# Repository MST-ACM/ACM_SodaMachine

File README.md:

# ACM Soda Machine Documentation
This documentation details all of information necessary to start, develop, maintain, and update the Soda Machine in CS 213.

## Dependencies
1. [Pyserial](https://github.com/pyserial/pyserial)
  + ```Pyserial``` handles the serial communication of authorization and logging characters between the Raspberry Pi and Arduino platforms in the soda machine.
2. [Pymysql](https://github.com/PyMySQL/PyMySQL)
  + ```Pymsql``` handles the connection to the SQL-lite database stored locally on the Raspberry Pi machine which stores the currency (i.e. how much money each user has).
3. [Libusb1](https://github.com/vpelletier/python-libusb1)
  + ```Libusb1``` handles the interfacing between the LCD screen and the Raspberry Pi so that the Raspberry Pi can write messages to the LCD.
4. [Evdev](https://python-evdev.readthedocs.io/en/latest/)
  + ```Evdev``` handles Kernel input interfacing for the magnetic strip reader when a user swipes their card.
5. [Nanpy](https://github.com/nanpy/nanpy)
  + ```Nanpy``` handles the direct throughput and communication to the arduino board through python.

## Installation
When migrating or reinstalling the system, please follow the following commands on the Raspberry Pi shell to install the main soda machine files ```NOT DEPENDENCIES```:
```
mkdir ~/pi/Soda-Machine/
cd ~/pi/Soda-Machine/
git init
git clone https://github.com/MST-ACM/ACM_SodaMachine_2.0.git
chmod +x main.py bin/smadmin bin/smdaemon
mv Documentation/sodamachine.init /etc/init.d/sodamachine
sudo update-rc.d sodamachine defaults
sudo service sodamachine restart
```
## Pseudocode Overview
1. The user swipes their Student ID into the magnetic strip reader which the magnetic strip reader translates to a ```Student ID```
2. ```Main.py``` performs a database lookup on the Student ID to determine if the user has the required funds.
3. If the database lookup is successful, the Raspberry Pi sends an authorization character to the Arduino using the serial connection.
  - If the database lookup is not successful the transaction fails and the Raspberry Pi resets it transaction state.
4. After the Arduino receives the authorization character, it waits for the user to press a button on the soda machine
  - If the user does not press a button after a certain amount of seconds, the transaction fails and the Raspberry Pi and Arduino reset their states.
5. After the user presses a button, the Arduino turns on the motor associated with the button until the soda is dispensed.
6. After the soda is dispensed, the Arduino sends a success character back to the Raspberry Pi so that the Raspberry Pi charges the user for the soda
  - The user is charged here instead of step 4 to prevent any errors with a soda failing to be dispensed.
7. Then, the Arduino and Raspberry Pi reset their states for the next transaction.

## Contribute
Please contact [acm@mst.edu](acm@mst.edu) if you would like to contribute to this project.

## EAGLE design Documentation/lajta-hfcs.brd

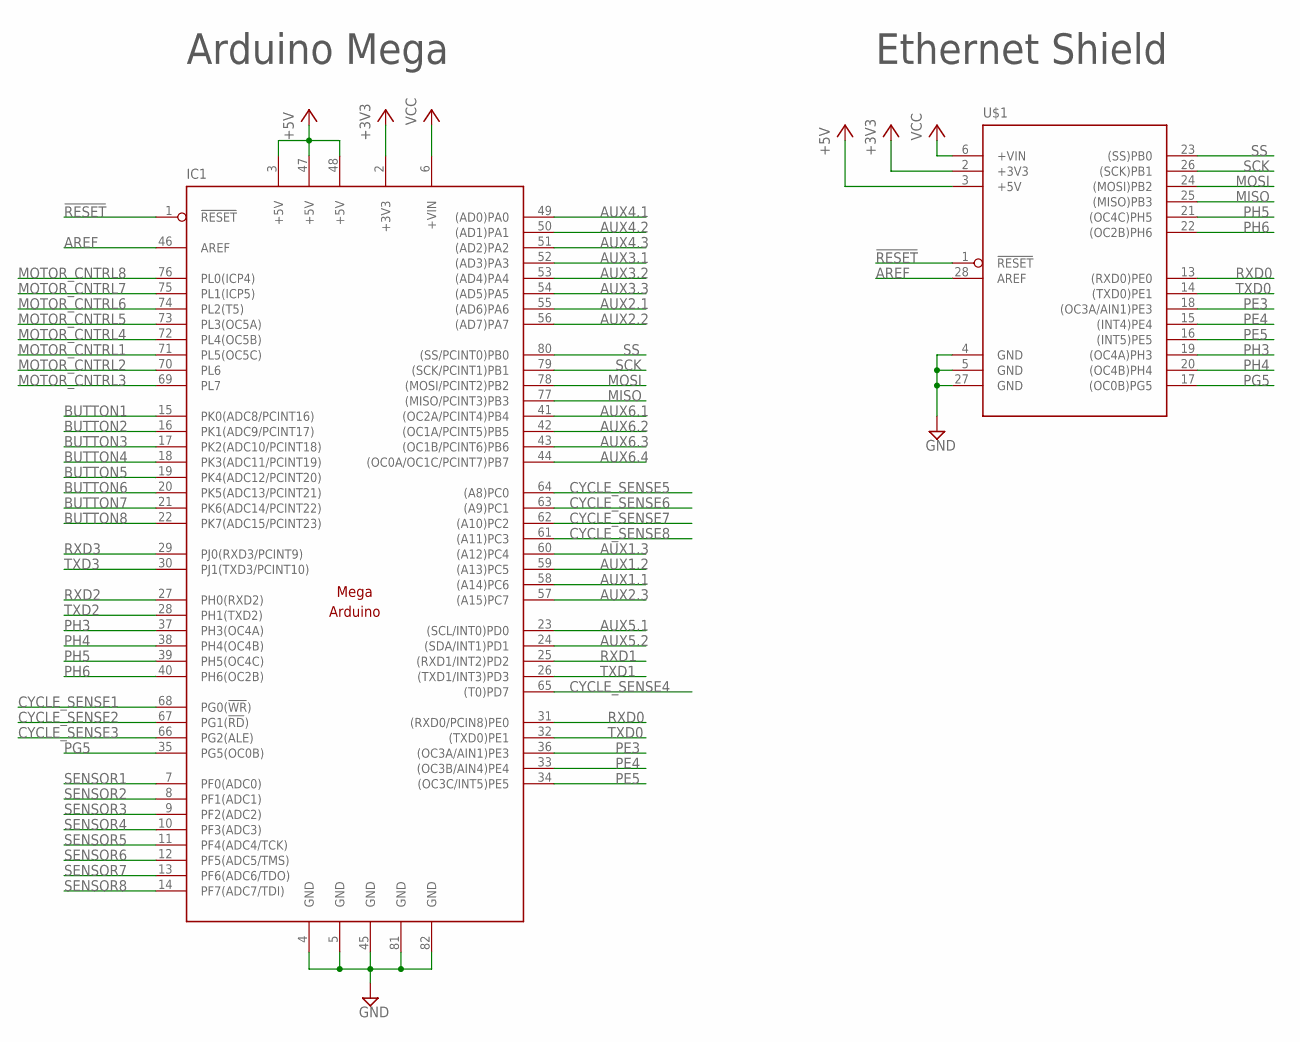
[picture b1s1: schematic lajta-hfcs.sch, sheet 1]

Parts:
IC1: MEGAARDUINO_1; MEGA_ARDUINO
U$1: MEGAARDUINO_ETHERNET_SHIELD; ETHERNET_SHIELD

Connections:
!RESET: IC1.1 (!RESET), U$1.1 (!RESET)
+3V3: IC1.2 (+3V3), U$1.2 (+3V3)
+5V: IC1.3 (+5V), IC1.47 (+5V), IC1.48 (+5V), U$1.3 (+5V); also elsewhere on the board
AREF: IC1.46 (AREF), U$1.28 (AREF)
AUX1.1: IC1.58 ((A14)PC6); also elsewhere on the board
AUX1.2: IC1.59 ((A13)PC5); also elsewhere on the board
AUX1.3: IC1.60 ((A12)PC4); also elsewhere on the board
AUX2.1: IC1.55 ((AD6)PA6); also elsewhere on the board
AUX2.2: IC1.56 ((AD7)PA7); also elsewhere on the board
AUX2.3: IC1.57 ((A15)PC7); also elsewhere on the board
AUX3.1: IC1.52 ((AD3)PA3); also elsewhere on the board
AUX3.2: IC1.53 ((AD4)PA4); also elsewhere on the board
AUX3.3: IC1.54 ((AD5)PA5); also elsewhere on the board
AUX4.1: IC1.49 ((AD0)PA0); also elsewhere on the board
AUX4.2: IC1.50 ((AD1)PA1); also elsewhere on the board
AUX4.3: IC1.51 ((AD2)PA2); also elsewhere on the board
AUX5.1: IC1.23 ((SCL/INT0)PD0); also elsewhere on the board
AUX5.2: IC1.24 ((SDA/INT1)PD1); also elsewhere on the board
AUX6.1: IC1.41 ((OC2A/PCINT4)PB4); also elsewhere on the board
AUX6.2: IC1.42 ((OC1A/PCINT5)PB5); also elsewhere on the board
AUX6.3: IC1.43 ((OC1B/PCINT6)PB6); also elsewhere on the board
AUX6.4: IC1.44 ((OC0A/OC1C/PCINT7)PB7); also elsewhere on the board
BUTTON1: IC1.15 (PK0(ADC8/PCINT16)); also elsewhere on the board
BUTTON2: IC1.16 (PK1(ADC9/PCINT17)); also elsewhere on the board
BUTTON3: IC1.17 (PK2(ADC10/PCINT18)); also elsewhere on the board
BUTTON4: IC1.18 (PK3(ADC11/PCINT19)); also elsewhere on the board
BUTTON5: IC1.19 (PK4(ADC12/PCINT20)); also elsewhere on the board
BUTTON6: IC1.20 (PK5(ADC13/PCINT21)); also elsewhere on the board
BUTTON7: IC1.21 (PK6(ADC14/PCINT22)); also elsewhere on the board
BUTTON8: IC1.22 (PK7(ADC15/PCINT23)); also elsewhere on the board
CYCLE_SENSE1: IC1.68 (PG0(!WR!)); also elsewhere on the board
CYCLE_SENSE2: IC1.67 (PG1(!RD!)); also elsewhere on the board
CYCLE_SENSE3: IC1.66 (PG2(ALE)); also elsewhere on the board
CYCLE_SENSE4: IC1.65 ((T0)PD7); also elsewhere on the board
CYCLE_SENSE5: IC1.64 ((A8)PC0); also elsewhere on the board
CYCLE_SENSE6: IC1.63 ((A9)PC1); also elsewhere on the board
CYCLE_SENSE7: IC1.62 ((A10)PC2); also elsewhere on the board
CYCLE_SENSE8: IC1.61 ((A11)PC3); also elsewhere on the board
GND: IC1.4 (GND), IC1.5 (GND), IC1.45 (GND), IC1.81 (GND), IC1.82 (GND), U$1.4 (GND), U$1.5 (GND), U$1.27 (GND); also elsewhere on the board
MISO: IC1.77 ((MISO/PCINT3)PB3), U$1.25 ((MISO)PB3); also elsewhere on the board
MOSI: IC1.78 ((MOSI/PCINT2)PB2), U$1.24 ((MOSI)PB2); also elsewhere on the board
MOTOR_CNTRL1: IC1.71 (PL5(OC5C)); also elsewhere on the board
MOTOR_CNTRL2: IC1.70 (PL6); also elsewhere on the board
MOTOR_CNTRL3: IC1.69 (PL7); also elsewhere on the board
MOTOR_CNTRL4: IC1.72 (PL4(OC5B)); also elsewhere on the board
MOTOR_CNTRL5: IC1.73 (PL3(OC5A)); also elsewhere on the board
MOTOR_CNTRL6: IC1.74 (PL2(T5)); also elsewhere on the board
MOTOR_CNTRL7: IC1.75 (PL1(ICP5)); also elsewhere on the board
MOTOR_CNTRL8: IC1.76 (PL0(ICP4)); also elsewhere on the board
PE3: IC1.36 ((OC3A/AIN1)PE3), U$1.18 ((OC3A/AIN1)PE3)
PE4: IC1.33 ((OC3B/AIN4)PE4), U$1.15 ((INT4)PE4)
PE5: IC1.34 ((OC3C/INT5)PE5), U$1.16 ((INT5)PE5)
PG5: IC1.35 (PG5(OC0B)), U$1.17 ((OC0B)PG5)
PH3: IC1.37 (PH3(OC4A)), U$1.19 ((OC4A)PH3)
PH4: IC1.38 (PH4(OC4B)), U$1.20 ((OC4B)PH4)
PH5: IC1.39 (PH5(OC4C)), U$1.21 ((OC4C)PH5)
PH6: IC1.40 (PH6(OC2B)), U$1.22 ((OC2B)PH6)
RXD0: IC1.31 ((RXD0/PCIN8)PE0), U$1.13 ((RXD0)PE0)
RXD1: IC1.25 ((RXD1/INT2)PD2); also elsewhere on the board
RXD2: IC1.27 (PH0(RXD2)); also elsewhere on the board
RXD3: IC1.29 (PJ0(RXD3/PCINT9)); also elsewhere on the board
SCK: IC1.79 ((SCK/PCINT1)PB1), U$1.26 ((SCK)PB1); also elsewhere on the board
SENSOR1: IC1.7 (PF0(ADC0)); also elsewhere on the board
SENSOR2: IC1.8 (PF1(ADC1)); also elsewhere on the board
SENSOR3: IC1.9 (PF2(ADC2)); also elsewhere on the board
SENSOR4: IC1.10 (PF3(ADC3)); also elsewhere on the board
SENSOR5: IC1.11 (PF4(ADC4/TCK)); also elsewhere on the board
SENSOR6: IC1.12 (PF5(ADC5/TMS)); also elsewhere on the board
SENSOR7: IC1.13 (PF6(ADC6/TDO)); also elsewhere on the board
SENSOR8: IC1.14 (PF7(ADC7/TDI)); also elsewhere on the board
SS: IC1.80 ((SS/PCINT0)PB0), U$1.23 ((SS)PB0); also elsewhere on the board
TXD0: IC1.32 ((TXD0)PE1), U$1.14 ((TXD0)PE1)
TXD1: IC1.26 ((TXD1/INT3)PD3); also elsewhere on the board
TXD2: IC1.28 (PH1(TXD2)); also elsewhere on the board
TXD3: IC1.30 (PJ1(TXD3/PCINT10)); also elsewhere on the board
VCC: IC1.6 (+VIN), U$1.6 (+VIN)

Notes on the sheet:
Arduino Mega
Ethernet Shield

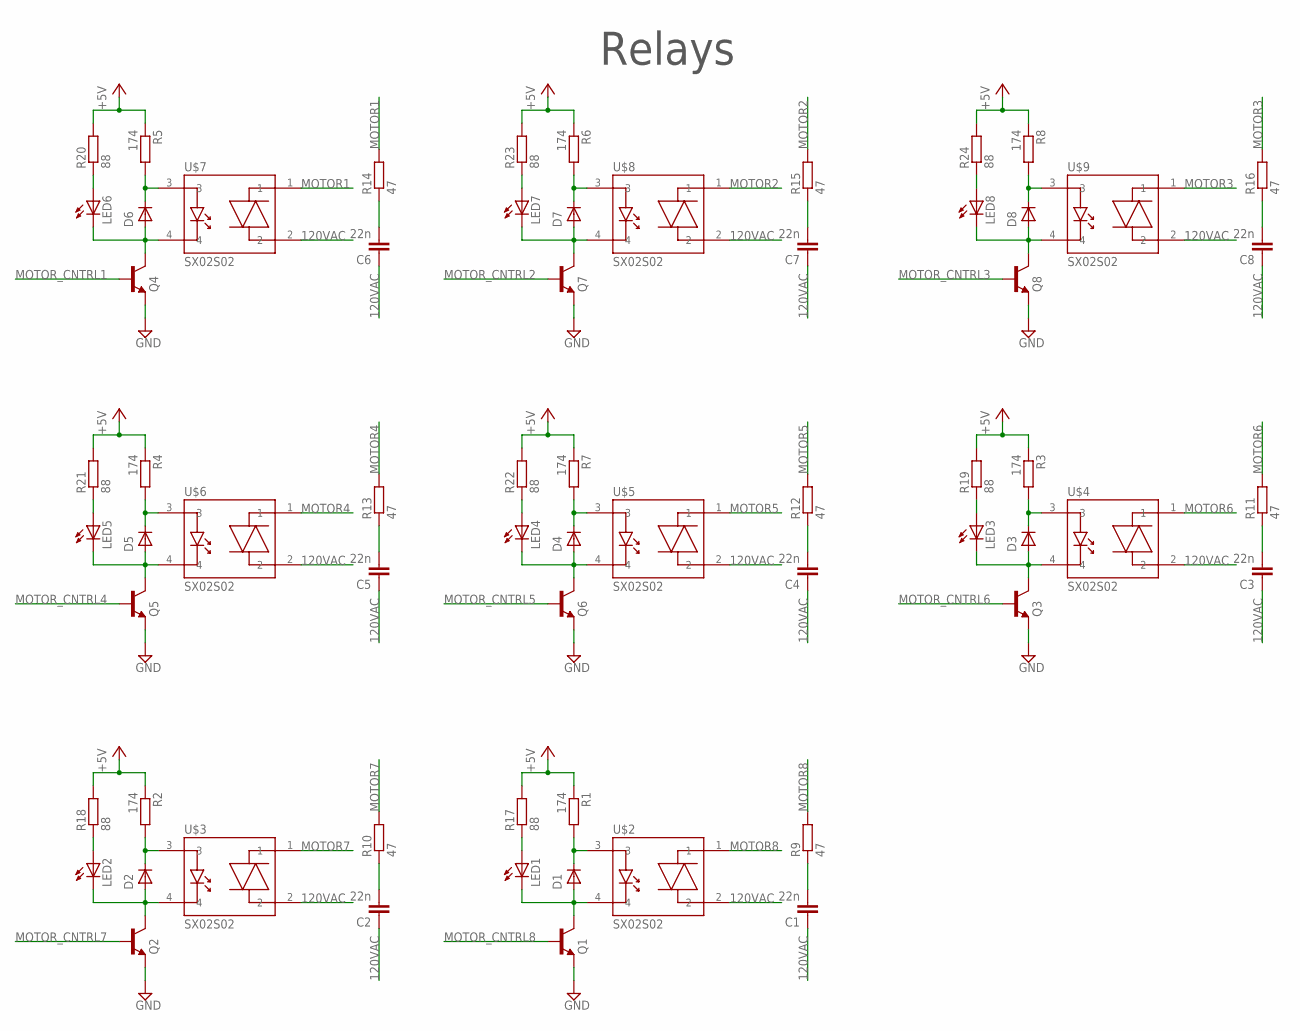
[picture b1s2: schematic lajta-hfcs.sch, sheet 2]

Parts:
C1, C2, C3, C4, C5, C6, C7, C8: 22n; C1812
D1, D2, D3, D4, D5, D6, D7, D8: 1N4448W; SOD123
LED1, LED2, LED3, LED4, LED5, LED6, LED7, LED8: LEDCHIPLED_0805; CHIPLED_0805
Q1, Q2, Q3, Q4, Q5, Q6, Q7, Q8: MMBT2222A; SOT23
R1, R2, R3, R4, R5, R6, R7, R8: 174; R0805
R9, R10, R11, R12, R13, R14, R15, R16: 47; R0805
R17, R18, R19, R20, R21, R22, R23, R24: 88; R0805
U$2, U$3, U$4, U$5, U$6, U$7, U$8, U$9: SX02S02; SIP-4

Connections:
120VAC: C1.1, C2.1, C3.1, C4.1, C5.1, C6.1, C7.1, C8.1, U$2.2, U$3.2, U$4.2, U$5.2, U$6.2, U$7.2, U$8.2, U$9.2; also elsewhere on the board
+5V: R1.1, R2.1, R3.1, R4.1, R5.1, R6.1, R7.1, R8.1, R17.2, R18.2, R19.2, R20.2, R21.2, R22.2, R23.2, R24.2; also elsewhere on the board
GND: Q1.2 (E), Q2.2 (E), Q3.2 (E), Q4.2 (E), Q5.2 (E), Q6.2 (E), Q7.2 (E), Q8.2 (E); also elsewhere on the board
MOTOR1: R14.2, U$7.1; also elsewhere on the board
MOTOR2: R15.2, U$8.1; also elsewhere on the board
MOTOR3: R16.2, U$9.1; also elsewhere on the board
MOTOR4: R13.2, U$6.1; also elsewhere on the board
MOTOR5: R12.2, U$5.1; also elsewhere on the board
MOTOR6: R11.2, U$4.1; also elsewhere on the board
MOTOR7: R10.2, U$3.1; also elsewhere on the board
MOTOR8: R9.2, U$2.1; also elsewhere on the board
MOTOR_CNTRL1: Q4.1 (B); also elsewhere on the board
MOTOR_CNTRL2: Q7.1 (B); also elsewhere on the board
MOTOR_CNTRL3: Q8.1 (B); also elsewhere on the board
MOTOR_CNTRL4: Q5.1 (B); also elsewhere on the board
MOTOR_CNTRL5: Q6.1 (B); also elsewhere on the board
MOTOR_CNTRL6: Q3.1 (B); also elsewhere on the board
MOTOR_CNTRL7: Q2.1 (B); also elsewhere on the board
MOTOR_CNTRL8: Q1.1 (B); also elsewhere on the board
unnamed: D1.C, R1.2, U$2.3
unnamed: D1.A, LED1.C, Q1.3 (C), U$2.4
unnamed: LED1.A, R17.1
unnamed: D2.C, R2.2, U$3.3
unnamed: D2.A, LED2.C, Q2.3 (C), U$3.4
unnamed: LED2.A, R18.1
unnamed: D3.C, R3.2, U$4.3
unnamed: D3.A, LED3.C, Q3.3 (C), U$4.4
unnamed: LED3.A, R19.1
unnamed: D4.C, R7.2, U$5.3
unnamed: D4.A, LED4.C, Q6.3 (C), U$5.4
unnamed: LED4.A, R22.1
unnamed: D5.C, R4.2, U$6.3
unnamed: D5.A, LED5.C, Q5.3 (C), U$6.4
unnamed: LED5.A, R21.1
unnamed: LED6.A, R20.1
unnamed: D6.A, LED6.C, Q4.3 (C), U$7.4
unnamed: D6.C, R5.2, U$7.3
unnamed: LED7.A, R23.1
unnamed: D7.A, LED7.C, Q7.3 (C), U$8.4
unnamed: D7.C, R6.2, U$8.3
unnamed: LED8.A, R24.1
unnamed: D8.A, LED8.C, Q8.3 (C), U$9.4
unnamed: D8.C, R8.2, U$9.3
unnamed: C8.2, R16.1
unnamed: C7.2, R15.1
unnamed: C4.2, R12.1
unnamed: C5.2, R13.1
unnamed: C6.2, R14.1
unnamed: C3.2, R11.1
unnamed: C2.2, R10.1
unnamed: C1.2, R9.1

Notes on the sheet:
Relays

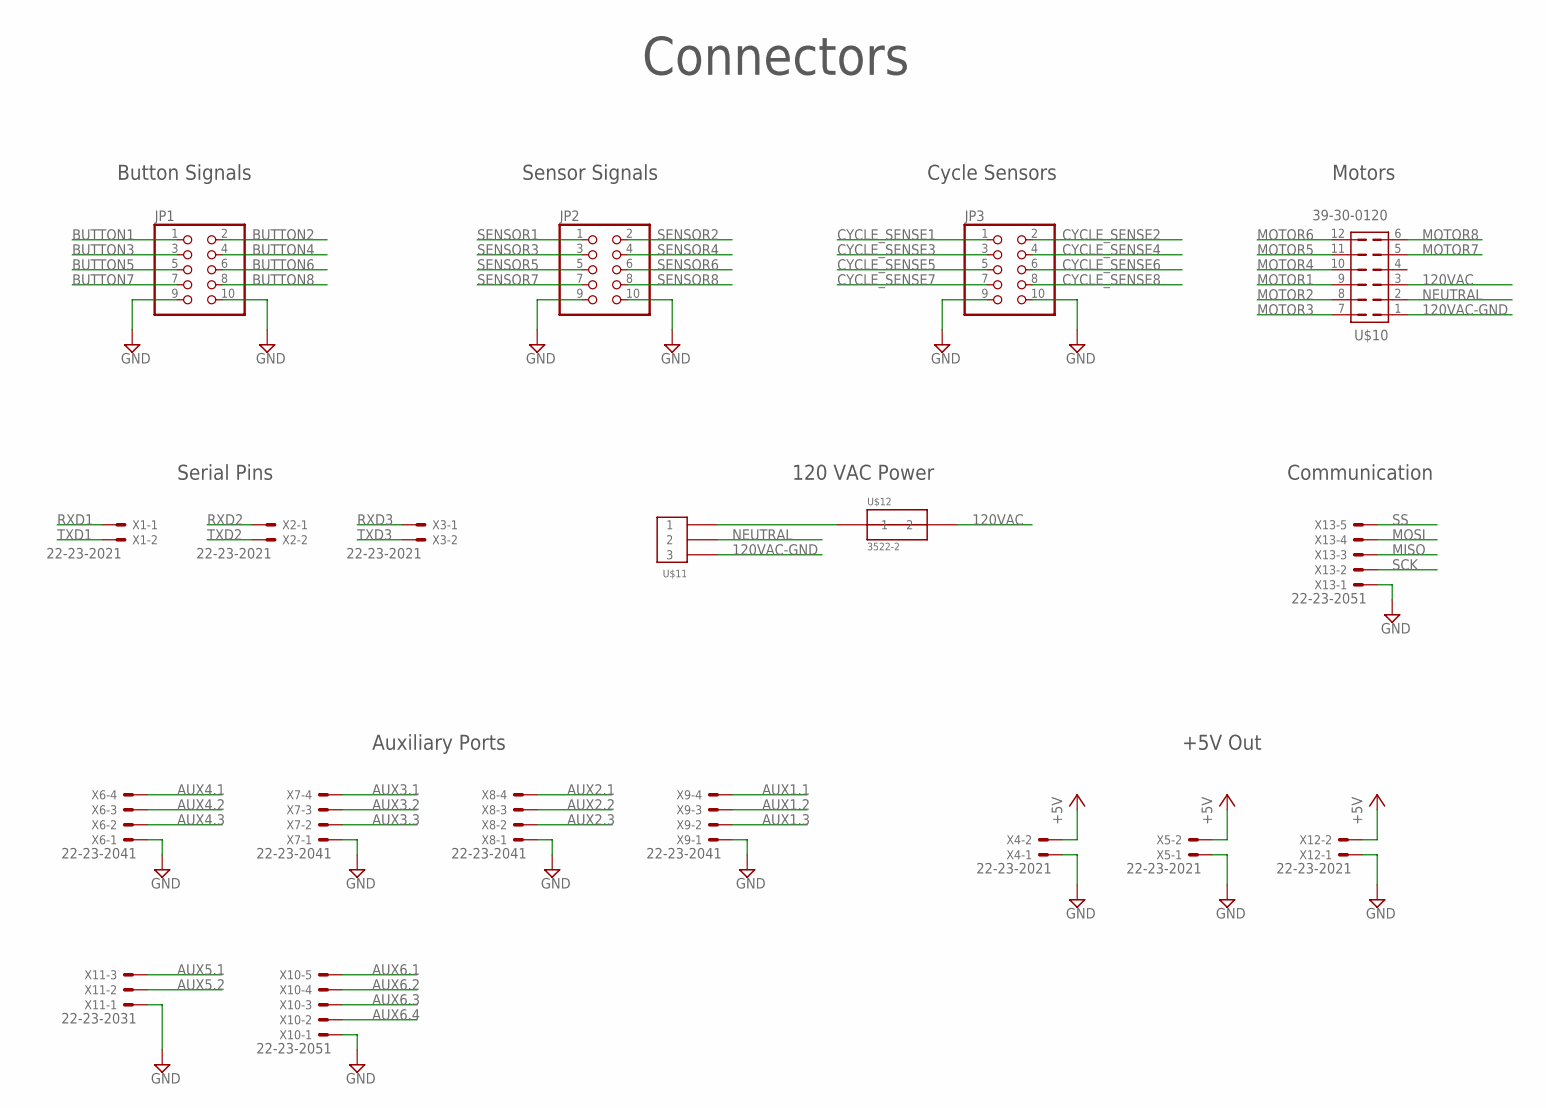
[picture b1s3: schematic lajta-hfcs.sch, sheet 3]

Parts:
JP1, JP2, JP3: PINHD-2X05_2.00; 2X05M
U$10: 39-30-0120; MINIFIT5569-2-6
U$11: 39-30-3035
U$12: 3522-2; ATC
X1, X2, X3, X4, X5, X12: 22-23-2021
X6, X7, X8, X9: 22-23-2041
X10, X13: 22-23-2051
X11: 22-23-2031

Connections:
120VAC: U$10.3, U$12.4 (2); also elsewhere on the board
120VAC-GND: U$10.1, U$11.3
+5V: X4.2, X5.2, X12.2; also elsewhere on the board
AUX1.1: X9.4; also elsewhere on the board
AUX1.2: X9.3; also elsewhere on the board
AUX1.3: X9.2; also elsewhere on the board
AUX2.1: X8.4; also elsewhere on the board
AUX2.2: X8.3; also elsewhere on the board
AUX2.3: X8.2; also elsewhere on the board
AUX3.1: X7.4; also elsewhere on the board
AUX3.2: X7.3; also elsewhere on the board
AUX3.3: X7.2; also elsewhere on the board
AUX4.1: X6.4; also elsewhere on the board
AUX4.2: X6.3; also elsewhere on the board
AUX4.3: X6.2; also elsewhere on the board
AUX5.1: X11.3; also elsewhere on the board
AUX5.2: X11.2; also elsewhere on the board
AUX6.1: X10.5; also elsewhere on the board
AUX6.2: X10.4; also elsewhere on the board
AUX6.3: X10.3; also elsewhere on the board
AUX6.4: X10.2; also elsewhere on the board
BUTTON1: JP1.1; also elsewhere on the board
BUTTON2: JP1.2; also elsewhere on the board
BUTTON3: JP1.3; also elsewhere on the board
BUTTON4: JP1.4; also elsewhere on the board
BUTTON5: JP1.5; also elsewhere on the board
BUTTON6: JP1.6; also elsewhere on the board
BUTTON7: JP1.7; also elsewhere on the board
BUTTON8: JP1.8; also elsewhere on the board
CYCLE_SENSE1: JP3.1; also elsewhere on the board
CYCLE_SENSE2: JP3.2; also elsewhere on the board
CYCLE_SENSE3: JP3.3; also elsewhere on the board
CYCLE_SENSE4: JP3.4; also elsewhere on the board
CYCLE_SENSE5: JP3.5; also elsewhere on the board
CYCLE_SENSE6: JP3.6; also elsewhere on the board
CYCLE_SENSE7: JP3.7; also elsewhere on the board
CYCLE_SENSE8: JP3.8; also elsewhere on the board
GND: JP1.9, JP1.10, JP2.9, JP2.10, JP3.9, JP3.10, X4.1, X5.1, X6.1, X7.1, X8.1, X9.1, X10.1, X11.1, X12.1, X13.1; also elsewhere on the board
MISO: X13.3; also elsewhere on the board
MOSI: X13.4; also elsewhere on the board
MOTOR1: U$10.9; also elsewhere on the board
MOTOR2: U$10.8; also elsewhere on the board
MOTOR3: U$10.7; also elsewhere on the board
MOTOR4: U$10.10; also elsewhere on the board
MOTOR5: U$10.11; also elsewhere on the board
MOTOR6: U$10.12; also elsewhere on the board
MOTOR7: U$10.5; also elsewhere on the board
MOTOR8: U$10.6; also elsewhere on the board
unnamed: U$11.1, U$12.1
NEUTRAL: U$10.2, U$11.2
RXD1: X1.1; also elsewhere on the board
RXD2: X2.1; also elsewhere on the board
RXD3: X3.1; also elsewhere on the board
SCK: X13.2; also elsewhere on the board
SENSOR1: JP2.1; also elsewhere on the board
SENSOR2: JP2.2; also elsewhere on the board
SENSOR3: JP2.3; also elsewhere on the board
SENSOR4: JP2.4; also elsewhere on the board
SENSOR5: JP2.5; also elsewhere on the board
SENSOR6: JP2.6; also elsewhere on the board
SENSOR7: JP2.7; also elsewhere on the board
SENSOR8: JP2.8; also elsewhere on the board
SS: X13.5; also elsewhere on the board
TXD1: X1.2; also elsewhere on the board
TXD2: X2.2; also elsewhere on the board
TXD3: X3.2; also elsewhere on the board

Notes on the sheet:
Connectors
Button Signals
Sensor Signals
Motors
Serial Pins
120 VAC Power
Cycle Sensors
+5V Out
Auxiliary Ports
Communication

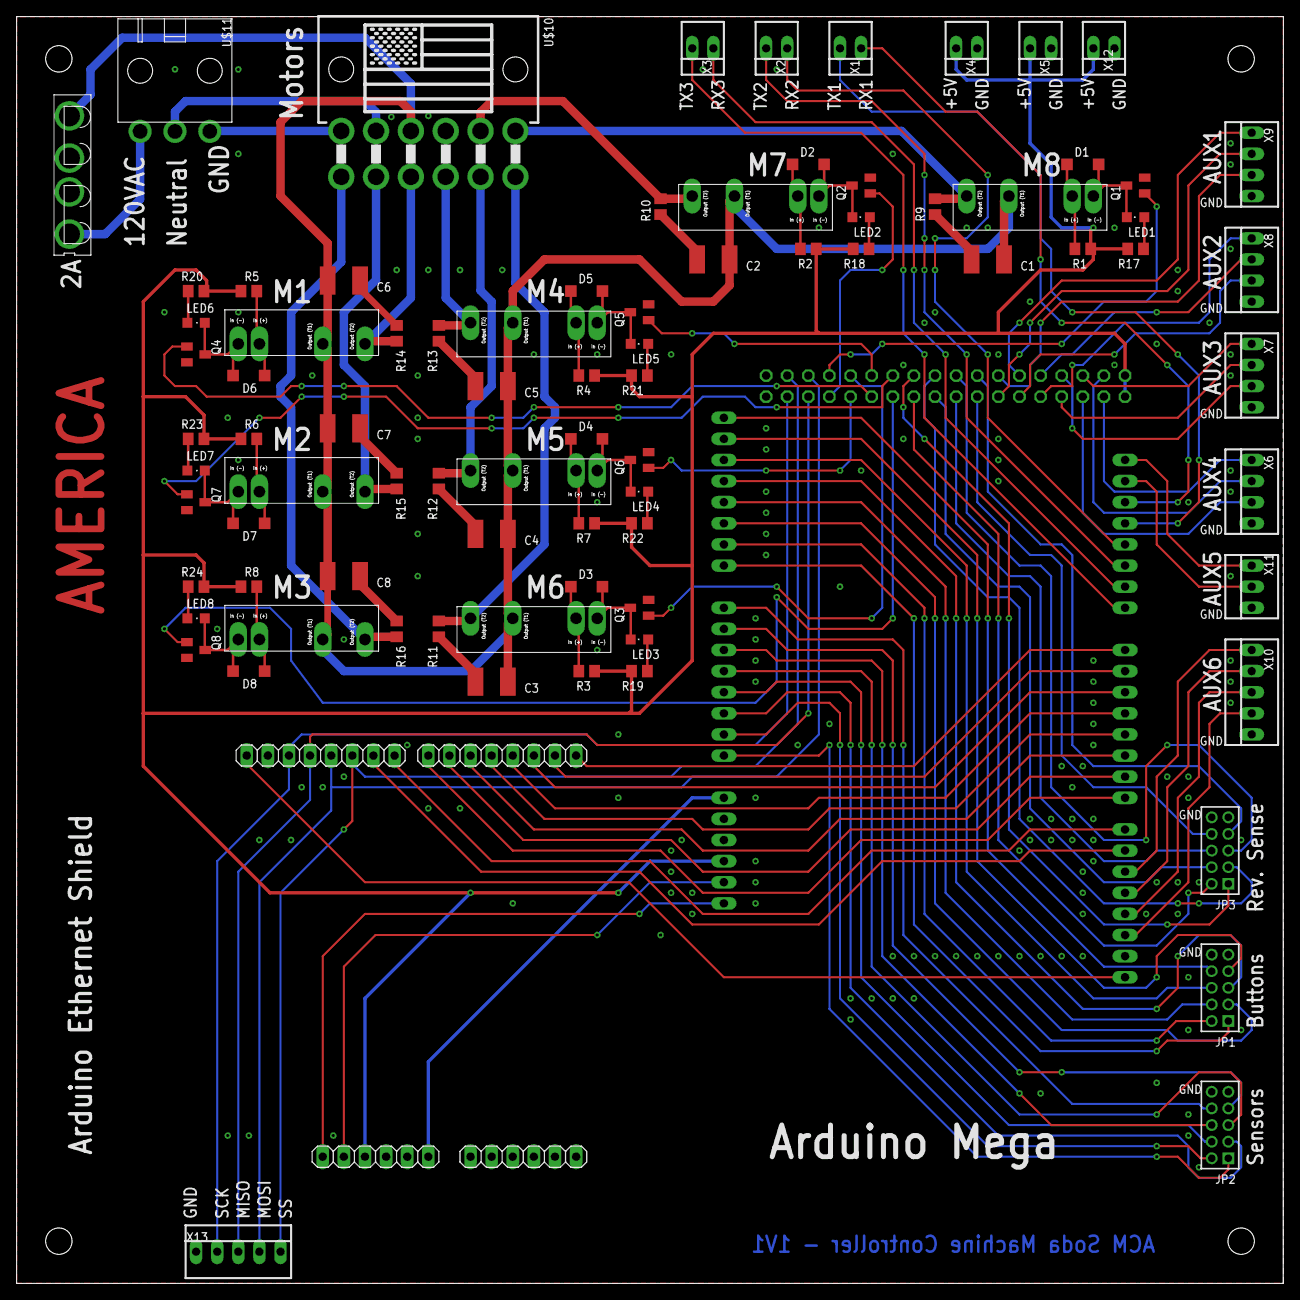
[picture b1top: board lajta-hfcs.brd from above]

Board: 2 copper layers, 152.4 x 152.4 mm, 85 parts (1 on the bottom side), 120 nets.

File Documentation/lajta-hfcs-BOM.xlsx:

Board Name: | lajta-hfcs | Quantity: | 2
Description: | Controller for ACM soda machine.
Board Vrsn: | 1V1 | Client: | ACM
Date: | 41773
Item # | Qty | Totals | Ref Des | Value | Manufacturer | Mfg Part # | Digikey Part # | Mouser Part # | Description | Package | Alt Mfg Part #s
PCB Assembly
1 | 8 | 16 | C1, C2, C3, C4, C5, C6, C7, C8 | 22n | Murata | GA243QR7E2223MW01L |  | 81-GA243QR7E2223MW1L | Multilayer Ceramic Capacitors MLCC - SMD/SMT .022uF 250Volts 20% | C1812
2 | 8 | 16 | D1, D2, D3, D4, D5, D6, D7, D8 | 1N4448W | Vishay | 1N4448W-E3-08 |  | 78-1N4448W-E3-08 | Diodes - General Purpose, Power, Switching 100 Volt 500mA 4ns | SOD123
3 | 1 | 2 | IC1-SNGL-HDR |  | TE | 5-826629-0 |  | 571-5-826629-0 | Headers & Wire Housings 50P SINGLE ROW | HDR
4 | 2 | 4 | IC1-DBL-HDR |  | Molex | 10-89-7361 |  | 538-10-89-7361 | Headers & Wire Housings 2.54MM HDR VT 2X18P 240/110 SNPB | HDR
5 | 3 | 6 | JP1, JP2, JP3 |  | 3M | 951210-8622-AR |  | 517-951210-8622-AR | Headers & Wire Housings 10P PIN STRP HDR 2R STRT PTH 10U AU | 2X05M
6 | 8 | 16 | LED1, LED2, LED3, LED4, LED5, LED6, LED7, LED8 |  | OSRAM Opto | LS R976-NR-1 |  | 720-LSR976-NR-1 | Standard LEDs - SMD Super Red, 633nm 180mcd, 20mA | CHIPLED_0805
7 | 8 | 16 | Q1, Q2, Q3, Q4, Q5, Q6, Q7, Q8 | MMBT2222A | Fairchild | MMBT2222A |  | 512-MMBT2222A | Transistors Bipolar - BJT SOT-23 NPN GEN PUR | SOT23
8 | 8 | 16 | R1, R2, R3, R4, R5, R6, R7, R8 | 174 | Vishay | CRCW0805174RFKEA |  | 71-CRCW0805-174-E3 | Thick Film Resistors - SMD 1/8watt 174ohms 1% 100ppm | R0805
9 | 8 | 16 | R9, R10, R11, R12, R13, R14, R15, R16 | 47 | Vishay | CRCW080547R0FKEB |  | 71-CRCW080547R0FKEB | Thick Film Resistors - SMD 1/8watt 47ohms 1% | R0805
10 | 8 | 16 | R17, R18, R19, R20, R21, R22, R23, R24 | 88 | Vishay | CRCW080588R7FKEA |  | 71-CRCW0805-88.7-E3 | Thick Film Resistors - SMD 1/8watt 88.7ohms 1% 100ppm | R0805
11 | 2 | 4 | U$1 | 1x8 | TE | 215297-8 |  | 571-215297-8 | Headers & Wire Housings 8P HV-100 FED-LEI | ETHERNET_SHIELD
12 | 2 | 4 | U$1 | 1x6 | TE | 215299-6 |  | 571-215299-6 | Headers & Wire Housings 6P RECPT VERT HV-100
13 | 8 | 16 | U$2, U$3, U$4, U$5, U$6, U$7, U$8, U$9 | SX02S02 | Sharp | S202S01F |  | 852-S202S01F | Solid State Relays - PCB Mount 4-SIP NON-ZC 8mA | SIP-4
14 | 1 | 2 | U$10 | 39-30-0120 | Molex | 39-30-0120 |  | 538-39-30-0120 | Headers & Wire Housings 12 CKT R/A HEADER | MINIFIT5569-2-6
15 | 1 | 2 | U$11 | 39-30-3035 | Molex | 39-30-3035 |  | 538-39-30-3035 | Headers & Wire Housings 3 CKT R/A HEADER
16 | 1 | 2 | U$12 | 3522 | Keystone | 3522-2 |  | 534-3522-2 | Fuse Holder AUTO FUSEHOLDER .025 | 3522-2
17 | 6 | 12 | X1, X2, X3, X4, X5, X12 | 22-23-2021 | Molex | 22-23-2021 |  | 538-22-23-2021 | Headers & Wire Housings VERT PCB HDR 2P TIN FRICTION LOCK | 22-23-2021
18 | 4 | 8 | X6, X7, X8, X9 | 22-23-2041 | Molex | 22-23-2041 |  | 538-22-23-2041 | Headers & Wire Housings VERT PCB HDR 4P TIN FRICTION LOCK | 22-23-2041
19 | 1 | 2 | X11 | 22-23-2031 | Molex | 22-23-2031 |  | 538-22-23-2031 | Headers & Wire Housings VERT PCB HDR 3P TIN FRICTION LOCK | 22-23-2031
20 | 2 | 4 | X10, X13 | 22-23-2051 | Molex | 22-23-2051 |  | 538-22-23-2051 | Headers & Wire Housings VERT PCB HDR 5P TIN FRICTION LOCK | 22-23-2051
Additional Parts (Mating connectors, fuse, crimp terminals, etc.)
21 | 1 | 2 | U$12 (Fuse) | 2A 32V | Cooper | BK/ATC-2 |  | 504-BK/ATC-2 | Automotive Fuses BUSS ATC FUSE | ATC
22 | 1 | 2 | U$11-Cable-End (Power Connector) | 39-01-4031 | Molex | 39-01-4031 |  | 538-39-01-4031 | Headers & Wire Housings 3 CKT RCPT HOUSING
23 | 1 | 2 | U$10-Mating-End (Motor Connector) | 39-01-2120 | Molex | 39-01-2120 |  | 538-39-01-2120 | Headers & Wire Housings 12 CKT RCPT HOUSING
24 | 15 | 30 | U$10-Crimp-Terminals | 39-00-0039 | Molex | 39-00-0039 |  | 538-39-00-0039 | Headers & Wire Housings SOCKET 24-18AWG BULK
25 | 3 | 6 | Ribbon-Cable-Female-Connector | 1-111623-8 | TE | 1-111623-8 |  | 571-1-111623-8 | Headers & Wire Housings 2MM REC 2X05P POL FEED THRU
26 | 1 | 2 | Arduino Mega | Mega | Arduino | A000067 |  | 782-A000067 | Development Boards & Kits - AVR ARDUINO MEGA2560 REV 3
27 | 1 | 2 | Arduino Ethernet Shield | Ethernet Shield | Arduino | A000072 |  | 782-A000072 | Ethernet Development Tools ARDUINO ETHERNET SHD MIC-SD W/O PoE REV 3
28 | 6 | 12 | X1, X2, X3, X4, X5, X12 (mating connector) | 22-01-2025 | Molex | 22-01-2025 |  | 538-22-01-2025 | Headers & Wire Housings 2 CRT CRIMP HOUSING | 6471
29 | 4 | 8 | X6, X7, X8, X9 (mating connector) | 22-01-2045 | Molex | 22-01-2045 |  | 538-22-01-2045 | Headers & Wire Housings 4 CRT TERM HOUSING | 6471
30 | 1 | 2 | X11 (mating connector) | 22-01-2035 | Molex | 22-01-2035 |  | 538-22-01-2035 | Headers & Wire Housings 3 CRT TERM HOUSING | 6471
31 | 2 | 4 | X10, X13 (mating connector) | 22-01-2055 | Molex | 22-01-2055 |  | 538-22-01-2055 | Headers & Wire Housings 5 CRT TERM HOUSING | 6471

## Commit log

2016-12-15 [ADD] Fix addUser implementation and Plug-And-Play
2017-01-25 [UPDATE] Python Requirements + Minor Fixes
